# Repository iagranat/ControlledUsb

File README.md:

# Controlled USB 2.0 Extension Cable

An intelligent USB 2.0 High-Speed (480 Mbps) inline extension cable with host-controlled power & data disconnection.

---

## 🛠️ System Architecture

```
                  +-------------------------------------------------------------+
                  |                     USB DONGLE                              |
                  |                                                             |
USB-A Male ------>| ===> CH334F 2-Port USB Hub                                  |
(From PC)         |       |                                                     |
                  |       +-- Port 1 ----> Waveshare RP2040-Zero (USB CDC Serial|
                  |       |                (GP16 = Onboard WS2812 RGB LED)      |
                  |       |                         |                           |
                  |       |             GP14 (PWR)  | GP15 (DATA)               |
                  |       |             Active HIGH | Active LOW                |
                  |       |                         v                           |
                  |       +-- Port 2 --+-> [CH440G High-Speed Switch] (D+/D-) ->|---> USB-A Female
                  |                    |                                        |     (Target Device)
                  |                    +-> [TPS22918 Load Switch] (VBUS, 2A) -->|
                  |                                                             |
                  |   GND (Common ground throughout) -------------------------->|
                  +-------------------------------------------------------------+
```

---

## 📌 Pinout & Connections

### RP2040-Zero
| RP2040 Pin | Connected To | Description / Logic |
| :--- | :--- | :--- |
| **GP16** | *Onboard WS2812* | Status RGB LED (Green = ON, Red = OFF, Yellow = Cycling, Blue = Charge) |
| **GP14** | **TPS22918** `ON` | High-side power switch enable (Active **HIGH**: `1` = 5V ON, `0` = 0V OFF) |
| **GP15** | **CH440G** `EN` | USB data switch output enable (Active **LOW**: `0` = Pass, `1` = Cut) |
| **GP26** | **Push Button** | Tactile button to GND (Internal pull-up enabled) |

---

## 🚦 RGB Status Indications

| Color | State | $V_{BUS}$ (Power) | $D+/D-$ (Data) | Description |
| :--- | :---: | :---: | :---: | :--- |
| 🟢 **Green** | `CONNECTED` | **ON** | **ON** | Normal operation. |
| 🔴 **Red** | `DISCONNECTED`| **OFF** | **OFF** | Completely unpowered and un-enumerated. |
| 🔵 **Blue** | `CHARGE_ONLY` | **ON** | **OFF** | Safe charging without data communication. |
| 🟡 **Yellow** *(Blinking)* | `CYCLING` | *Rebooting* | *Rebooting* | Active reboot/cycle in progress. |

---

## 🕹️ Controls

### 1. Serial Commands (115200 baud, Newline)
* `ON` or `CONNECT` — Connect power and data (with safe sequencing).
* `OFF` or `DISCONNECT` — Disconnect data first, then cut power.
* `CHARGE` — Keep 5V active, cut data lines.
* `CYCLE <ms>` — Reboot port for specified milliseconds (e.g. `CYCLE 1500`).
* `STATUS` or `?` — Query current state.
* `HELP` — List commands.

### 2. Physical Button
* **Short Click (< 1.2s)**: Toggle between `CONNECTED` and `DISCONNECTED`.
* **Long Press (> 1.2s)**: Trigger automated 1-second power cycle (`CYCLE 1000`).

---

## 🚀 Building & Flashing with PlatformIO

1. Plug the **RP2040-Zero** into your PC while holding the **`BOOT`** button.
2. Open this folder in Antigravity IDE (with the PlatformIO extension installed).
3. Click the **Build** (`✓`) button in the bottom status bar.
4. Click the **Upload** (`→`) button to flash the firmware.
5. Click the **Serial Monitor** (`🔌`) button to open the terminal.

---

## 🐍 Python CLI Utility

Run from the `tools/` folder:
```powershell
python switch_cli.py on
python switch_cli.py off
python switch_cli.py cycle 1000
python switch_cli.py status
```

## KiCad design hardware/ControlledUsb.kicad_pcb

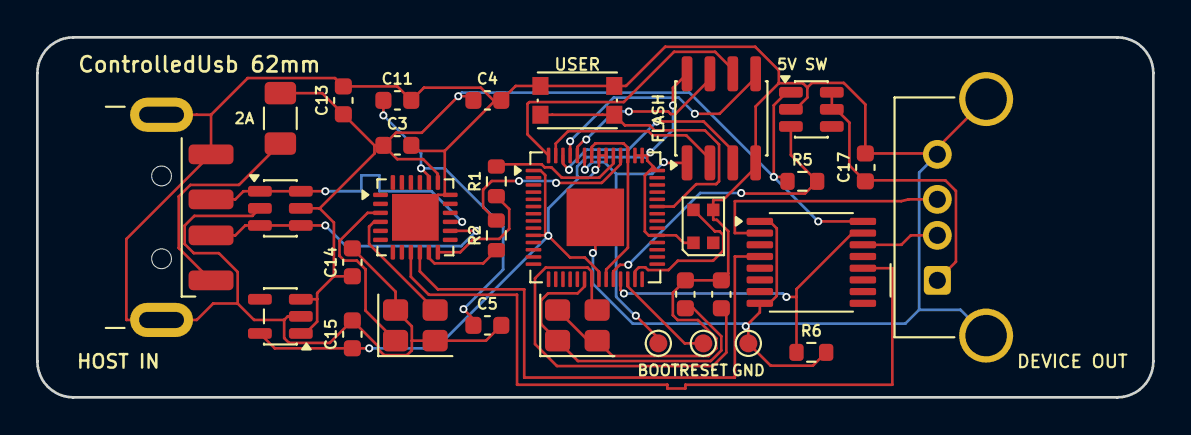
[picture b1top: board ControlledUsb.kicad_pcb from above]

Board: 4 copper layers, 62.0 x 20.0 mm, 31 parts (0 on the bottom side), 32 nets.

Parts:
C1, C2: 15pF; C_0603_1608Metric
C3, C4, C5: 100nF; C_0603_1608Metric
C11: 1uF; C_0603_1608Metric
C13, C14, C15, C17: 10uF; C_0603_1608Metric
D1: WS2812B; LED_WS2812B-2020_PLCC4_2.0x2.0mm
F1: PTC 2A; Fuse_1206_3216Metric
J1: USB_A_Male; USB_A_CNCTech_1001-011-01101_Horizontal
J2: USB_A_Female; USB_A_Molex_67643_Horizontal
R1, R2: 27R; R_0603_1608Metric
R5, R6: 10k; R_0603_1608Metric
SW1: USER_BTN; SW_Push_1P1T_NO_CK_KMR2
TP1: BOOT; TestPoint_Pad_D1.0mm
TP2: RESET; TestPoint_Pad_D1.0mm
TP3: GND; TestPoint_Pad_D1.0mm
U1: RP2040; QFN-56-1EP_7x7mm_P0.4mm_EP3.2x3.2mm
U2: W25Q32; SOIC-8_3.9x4.9mm_P1.27mm
U3: CH334F; QFN-24-1EP_4x4mm_P0.5mm_EP2.6x2.6mm
U4: TPS22918; SOT-23-6
U5: CH440P; TSSOP-16_4.4x5mm_P0.65mm
U6: ME6211C33; SOT-23-5
U7: USBLC6-2SC6; SOT-23-6
Y1, Y2: 12.000MHz; Crystal_SMD_3225-4Pin_3.2x2.5mm

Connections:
+1V1: U1.23, U1.45, U1.50
+3V3: C15.1, D1.1, U1.1, U1.10, U1.22, U1.33, U1.42, U1.43, U1.44, U1.48, U1.49, U2.8, U6.5
+5V: F1.1, J1.1
+5V_FUSED: C3.1, C4.1, C13.1, C14.1, F1.2, R5.1, U3.19, U4.1, U5.16, U6.1, U6.3, U7.5
DATA_OE_N: R6.1, U1.25, U5.15
GND: C1.2, C2.2, C3.2, C4.2, C5.2, C11.2, C13.2, C14.2, C15.2, C17.2, D1.3, J1.4, J1.SH, J2.4, J2.SH, R6.2, SW1.1, TP3.1, U1.57, U2.4, U3.18, U3.25, U4.2, U5.1, U5.8, U6.2, U7.2, Y1.2, Y1.4, Y2.2, Y2.4
HUB_PORT1_DM: R2.1, U3.11
HUB_PORT1_DP: R1.1, U3.12
HUB_PORT2_DM: U3.9, U5.12
HUB_PORT2_DP: U3.10, U5.4
HUB_V33: C5.1, C11.1, U3.20
HUB_XI: U3.3, Y2.1
HUB_XO: U3.4, Y2.3
MCU_USB_DM: R2.2, U1.46
MCU_USB_DP: R1.2, U1.47
MCU_XI: C1.1, U1.20, Y1.1
MCU_XO: C2.1, U1.21, Y1.3
PWR_EN: R5.2, U1.24, U4.3
QSPI_SCLK: U1.56, U2.6
QSPI_SD0: U1.53, U2.5
QSPI_SD1: U1.55, U2.2
QSPI_SD2: U1.54, U2.3
QSPI_SD3: U1.52, U2.7
QSPI_SS: TP1.1, U1.51, U2.1
RGB_DIN: D1.4, U1.27
RUN: TP2.1, U1.26
SW_DM: J2.2, U5.14
SW_DP: J2.3, U5.2
USB_HOST_DM: J1.2, U3.14, U7.3, U7.4
USB_HOST_DP: J1.3, U3.15, U7.1, U7.6
USER_BTN: SW1.2, U1.37
VBUS_SW: C17.1, J2.1, U4.5, U4.6

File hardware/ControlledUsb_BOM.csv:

"Refs","Value","Footprint","Qty","DNP"
"C1,C2","15pF","Capacitor_SMD:C_0603_1608Metric","2",""
"C3-C5","100nF","Capacitor_SMD:C_0603_1608Metric","3",""
"C11","1uF","Capacitor_SMD:C_0603_1608Metric","1",""
"C13-C15,C17","10uF","Capacitor_SMD:C_0603_1608Metric","4",""
"D1","WS2812B","LED_SMD:LED_WS2812B-2020_PLCC4_2.0x2.0mm","1",""
"F1","PTC 2A","Fuse:Fuse_1206_3216Metric","1",""
"J1","USB_A_Male","Connector_USB:USB_A_CNCTech_1001-011-01101_Horizontal","1",""
"J2","USB_A_Female","Connector_USB:USB_A_Molex_67643_Horizontal","1",""
"R1,R2","27R","Resistor_SMD:R_0603_1608Metric","2",""
"R5,R6","10k","Resistor_SMD:R_0603_1608Metric","2",""
"SW1","USER_BTN","Button_Switch_SMD:SW_Push_1P1T_NO_CK_KMR2","1",""
"TP1","BOOT","TestPoint:TestPoint_Pad_D1.0mm","1",""
"TP2","RESET","TestPoint:TestPoint_Pad_D1.0mm","1",""
"TP3","GND","TestPoint:TestPoint_Pad_D1.0mm","1",""
"U1","RP2040","Package_DFN_QFN:QFN-56-1EP_7x7mm_P0.4mm_EP3.2x3.2mm","1",""
"U2","W25Q32","Package_SO:SOIC-8_3.9x4.9mm_P1.27mm","1",""
"U3","CH334F","Package_DFN_QFN:QFN-24-1EP_4x4mm_P0.5mm_EP2.6x2.6mm","1",""
"U4","TPS22918","Package_TO_SOT_SMD:SOT-23-6","1",""
"U5","CH440P","Package_SO:TSSOP-16_4.4x5mm_P0.65mm","1",""
"U6","ME6211C33","Package_TO_SOT_SMD:SOT-23-5","1",""
"U7","USBLC6-2SC6","Package_TO_SOT_SMD:SOT-23-6","1",""
"Y1,Y2","12.000MHz","Crystal:Crystal_SMD_3225-4Pin_3.2x2.5mm","2",""

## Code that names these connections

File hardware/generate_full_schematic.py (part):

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				(pin output line (at -22.86 10.16 0) (length 2.54) (name "XOUT" (effects (font (size 1.27 1.27)))) (number "21" (effects (font (size 1.27 1.27)))))
				(pin bidirectional line (at -22.86 5.08 0) (length 2.54) (name "USB_DM" (effects (font (size 1.27 1.27)))) (number "46" (effects (font (size 1.27 1.27)))))
				(pin bidirectional line (at -22.86 2.54 0) (length 2.54) (name "USB_DP" (effects (font (size 1.27 1.27)))) (number "47" (effects (font (size 1.27 1.27)))))
				(pin bidirectional line (at -22.86 -2.54 0) (length 2.54) (name "QSPI_SS" (effects (font (size 1.27 1.27)))) (number "51" (effects (font (size 1.27 1.27)))))
				(pin bidirectional line (at -22.86 -5.08 0) (length 2.54) (name "QSPI_SD0" (effects (font (size 1.27 1.27)))) (number "53" (effects (font (size 1.27 1.27)))))
				(pin bidirectional line (at -22.86 -7.62 0) (length 2.54) (name "QSPI_SD1" (effects (font (size 1.27 1.27)))) (number "55" (effects (font (size 1.27 1.27)))))
				(pin bidirectional line (at -22.86 -10.16 0) (length 2.54) (name "QSPI_SD2" (effects (font (size 1.27 1.27)))) (number "54" (effects (font (size 1.27 1.27)))))
				(pin bidirectional line (at -22.86 -12.7 0) (length 2.54) (name "QSPI_SD3" (effects (font (size 1.27 1.27)))) (number "52" (effects (font (size 1.27 1.27)))))
				(pin bidirectional line (at -22.86 -15.24 0) (length 2.54) (name "QSPI_SCLK" (effects (font (size 1.27 1.27)))) (number "56" (effects (font (size 1.27 1.27)))))
				(pin input line (at -22.86 -20.32 0) (length 2.54) (name "RUN" (effects (font (size 1.27 1.27)))) (number "26" (effects (font (size 1.27 1.27)))))
				(pin bidirectional line (at 22.86 12.7 180) (length 2.54) (name "GP14(PWR)" (effects (font (size 1.27 1.27)))) (number "24" (effects (font (size 1.27 1.27)))))
				(pin bidirectional line (at 22.86 10.16 180) (length 2.54) (name "GP15(DATA)" (effects (font (size 1.27 1.27)))) (number "25" (effects (font (size 1.27 1.27)))))
				(pin bidirectional line (at 22.86 5.08 180) (length 2.54) (name "GP16(RGB)" (effects (font (size 1.27 1.27)))) (number "27" (effects (font (size 1.27 1.27)))))
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    add_wire(42.62, 42.46, 50, 42.46)
    add_label("VBUS_RAW", 50, 42.46)
    add_wire(42.62, 45.0, 50, 45.0)
    add_label("USB_HOST_DM", 50, 45.0)
    add_wire(42.62, 47.54, 50, 47.54)
    add_label("USB_HOST_DP", 50, 47.54)
    add_wire(42.62, 50.08, 48, 50.08)
    add_pwr("ControlledUsb:GND", "GND", 48, 50.08)
    add_wire(42.62, 52.62, 48, 52.62)
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    # U7
    add_sym("ControlledUsb:USBLC6-2SC6", "U7", "USBLC6-2SC6", "Package_TO_SOT_SMD:SOT-23-6", 95, 45, ["1", "2", "3", "4", "5", "6"])
    add_wire(84.84, 45.0, 78, 45.0)
    add_label("USB_HOST_DM", 78, 45.0, 180)
    add_wire(84.84, 47.54, 78, 47.54)
    add_label("USB_HOST_DP", 78, 47.54, 180)
    add_wire(95, 39.92, 95, 36)
    add_pwr("ControlledUsb:+5V", "+5V", 95, 36)
    add_wire(95, 55.16, 95, 58)
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    add_wire(284.92, 33.49, 284.92, 30)
    add_pwr("ControlledUsb:+5V", "+5V", 284.92, 30)
    add_wire(295.08, 33.49, 295.08, 30)
    add_label("HUB_V33", 295.08, 30, 90)
    add_wire(290, 69.05, 290, 73)
    add_pwr("ControlledUsb:GND", "GND", 290, 73)

    add_wire(272.22, 42.38, 262, 42.38)
    add_label("USB_HOST_DP", 262, 42.38, 180)
    add_wire(272.22, 44.92, 262, 44.92)
    add_label("USB_HOST_DM", 262, 44.92, 180)
    add_wire(272.22, 62.7, 262, 62.7)
    add_pwr("ControlledUsb:GND", "GND", 262, 62.7)

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
    add_sym("ControlledUsb:C_Small", "C11", "1uF", "Capacitor_SMD:C_0603_1608Metric", 340, 35, ["1", "2"])
    add_wire(340, 32.46, 340, 28)
    add_label("HUB_V33", 340, 28, 90)
    add_wire(340, 37.54, 340, 41)
    add_pwr("ControlledUsb:GND", "GND", 340, 41)

    add_sym("ControlledUsb:C_Small", "C5", "100nF", "Capacitor_SMD:C_0603_1608Metric", 355, 35, ["1", "2"])
    add_wire(355, 32.46, 355, 28)
    add_label("HUB_V33", 355, 28, 90)
    add_wire(355, 37.54, 355, 41)
    add_pwr("ControlledUsb:GND", "GND", 355, 41)

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    add_sym("ControlledUsb:R_Small", "R1", "27R", "Resistor_SMD:R_0603_1608Metric", 325, 42.38, ["1", "2"], rot=90)
    add_wire(307.78, 42.38, 322.46, 42.38)
    add_wire(327.54, 42.38, 335, 42.38)
    add_label("MCU_USB_DP", 335, 42.38)

    add_sym("ControlledUsb:R_Small", "R2", "27R", "Resistor_SMD:R_0603_1608Metric", 325, 44.92, ["1", "2"], rot=90)
    add_wire(307.78, 44.92, 322.46, 44.92)
    add_wire(327.54, 44.92, 335, 44.92)
    add_label("MCU_USB_DM", 335, 44.92)

    # Port 2 to CH440P
    add_wire(307.78, 50.0, 320, 50.0)
    add_label("HUB_PORT2_DP", 320, 50.0)
    add_wire(307.78, 52.54, 320, 52.54)
    add_label("HUB_PORT2_DM", 320, 52.54)

    # -------------------------------------------------------------
    # BLOCK 4: RP2040 MCU CORE & CLOCK (25..120, 110..220)
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
    # USB
    add_wire(52.14, 154.92, 45, 154.92)
    add_label("MCU_USB_DM", 45, 154.92, 180)
    add_wire(52.14, 157.46, 45, 157.46)
    add_label("MCU_USB_DP", 45, 157.46, 180)

    # QSPI
    add_wire(52.14, 162.54, 45, 162.54)
    add_label("QSPI_SS", 45, 162.54, 180)
    add_wire(52.14, 165.08, 45, 165.08)
    add_label("QSPI_SD0", 45, 165.08, 180)
    add_wire(52.14, 167.62, 45, 167.62)
    add_label("QSPI_SD1", 45, 167.62, 180)
    add_wire(52.14, 170.16, 45, 170.16)
    add_label("QSPI_SD2", 45, 170.16, 180)
    add_wire(52.14, 172.7, 45, 172.7)
    add_label("QSPI_SD3", 45, 172.7, 180)
    add_wire(52.14, 175.24, 45, 175.24)
    add_label("QSPI_SCLK", 45, 175.24, 180)

    # Control
    add_wire(52.14, 180.32, 45, 180.32)
    add_label("RUN", 45, 180.32, 180)
    add_wire(97.86, 147.3, 108, 147.3)
    add_label("PWR_EN", 108, 147.3)
    add_wire(97.86, 149.84, 108, 149.84)
    add_label("DATA_OE_N", 108, 149.84)
    add_wire(97.86, 154.92, 108, 154.92)
    add_label("RGB_DIN", 108, 154.92)
    add_wire(97.86, 160.0, 108, 160.0)
    add_label("USER_BTN", 108, 160.0)

    # Crystal Y1 & C1, C2
    add_sym("ControlledUsb:Crystal_GND24", "Y1", "12.000MHz", "Crystal:Crystal_SMD_3225-4Pin_3.2x2.5mm", 30, 148.5, ["1", "2", "3", "4"])
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    add_text("BLOCK 5: FLASH MEMORY & PADS", 130, 110)
    add_sym("ControlledUsb:W25Q32", "U2", "W25Q32", "Package_SO:SOIC-8_3.9x4.9mm_P1.27mm", 155, 145, ["1", "2", "3", "4", "5", "6", "7", "8"])
    add_wire(142.3, 142.46, 135, 142.46)
    add_label("QSPI_SS", 135, 142.46, 180)
    add_wire(142.3, 145.0, 135, 145.0)
    add_label("QSPI_SD0", 135, 145.0, 180)
    add_wire(142.3, 147.54, 135, 147.54)
    add_label("QSPI_SD2", 135, 147.54, 180)
    add_wire(142.3, 150.08, 135, 150.08)
    add_label("QSPI_SCLK", 135, 150.08, 180)

    add_wire(167.7, 145.0, 175, 145.0)
    add_label("QSPI_SD1", 175, 145.0)
    add_wire(167.7, 147.54, 175, 147.54)
    add_label("QSPI_SD3", 175, 147.54)
    add_wire(155, 137.38, 155, 133)
    add_pwr("ControlledUsb:+3V3", "+3V3", 155, 133)
    add_wire(155, 155.16, 155, 159)
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    # Test Pads
    add_sym("ControlledUsb:TestPoint", "TP1", "BOOT", "TestPoint:TestPoint_Pad_D1.0mm", 140, 180, ["1"])
    add_wire(137.46, 180, 130, 180)
    add_label("QSPI_SS", 130, 180, 180)

    add_sym("ControlledUsb:TestPoint", "TP2", "RESET", "TestPoint:TestPoint_Pad_D1.0mm", 155, 180, ["1"])
    add_wire(152.46, 180, 145, 180)
    add_label("RUN", 145, 180, 180)

    add_sym("ControlledUsb:TestPoint", "TP3", "GND", "TestPoint:TestPoint_Pad_D1.0mm", 170, 180, ["1"])
    add_wire(167.46, 180, 162, 180)
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    add_wire(229.84, 145.0, 222, 145.0)
    add_pwr("ControlledUsb:+5V", "+5V", 222, 145.0)
    add_wire(229.84, 150.08, 220, 150.08)
    add_label("PWR_EN", 220, 150.08, 180)
    add_wire(240, 155.16, 240, 160)
    add_pwr("ControlledUsb:GND", "GND", 240, 160)

    add_wire(250.16, 147.54, 255, 147.54)
    add_wire(255, 147.54, 255, 145.0)
    add_wire(250.16, 145.0, 265, 145.0)
    add_label("VBUS_SW", 265, 145.0)

    # R5 & C17
    add_sym("ControlledUsb:R_Small", "R5", "10k", "Resistor_SMD:R_0603_1608Metric", 215, 165, ["1", "2"])
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    add_wire(334.76, 137.38, 325, 137.38)
    add_pwr("ControlledUsb:GND", "GND", 325, 137.38)
    add_wire(334.76, 139.92, 320, 139.92)
    add_label("DATA_OE_N", 320, 139.92, 180)
    add_wire(334.76, 145.0, 320, 145.0)
    add_label("HUB_PORT2_DP", 320, 145.0, 180)
    add_wire(334.76, 147.54, 320, 147.54)
    add_label("HUB_PORT2_DM", 320, 147.54, 180)

    add_wire(365.24, 145.0, 375, 145.0)
    add_label("SW_DP", 375, 145.0)
    add_wire(365.24, 147.54, 375, 147.54)
    add_label("SW_DM", 375, 147.54)

    # R6
    add_sym("ControlledUsb:R_Small", "R6", "10k", "Resistor_SMD:R_0603_1608Metric", 315, 155, ["1", "2"])
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    add_text("BLOCK 8: DOWNSTREAM USB-A PORT", 270, 210)
    add_sym("ControlledUsb:USB_A_Receptacle", "J2", "USB_A_Female", "Connector_USB:USB_A_Molex_67643_Horizontal", 340, 240, ["1", "2", "3", "4", "5"])
    add_wire(332.38, 237.46, 320, 237.46)
    add_label("VBUS_SW", 320, 237.46, 180)
    add_wire(332.38, 240.0, 320, 240.0)
    add_label("SW_DM", 320, 240.0, 180)
    add_wire(332.38, 242.54, 320, 242.54)
    add_label("SW_DP", 320, 242.54, 180)
    add_wire(332.38, 245.08, 320, 245.08)
    add_pwr("ControlledUsb:GND", "GND", 320, 245.08)
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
